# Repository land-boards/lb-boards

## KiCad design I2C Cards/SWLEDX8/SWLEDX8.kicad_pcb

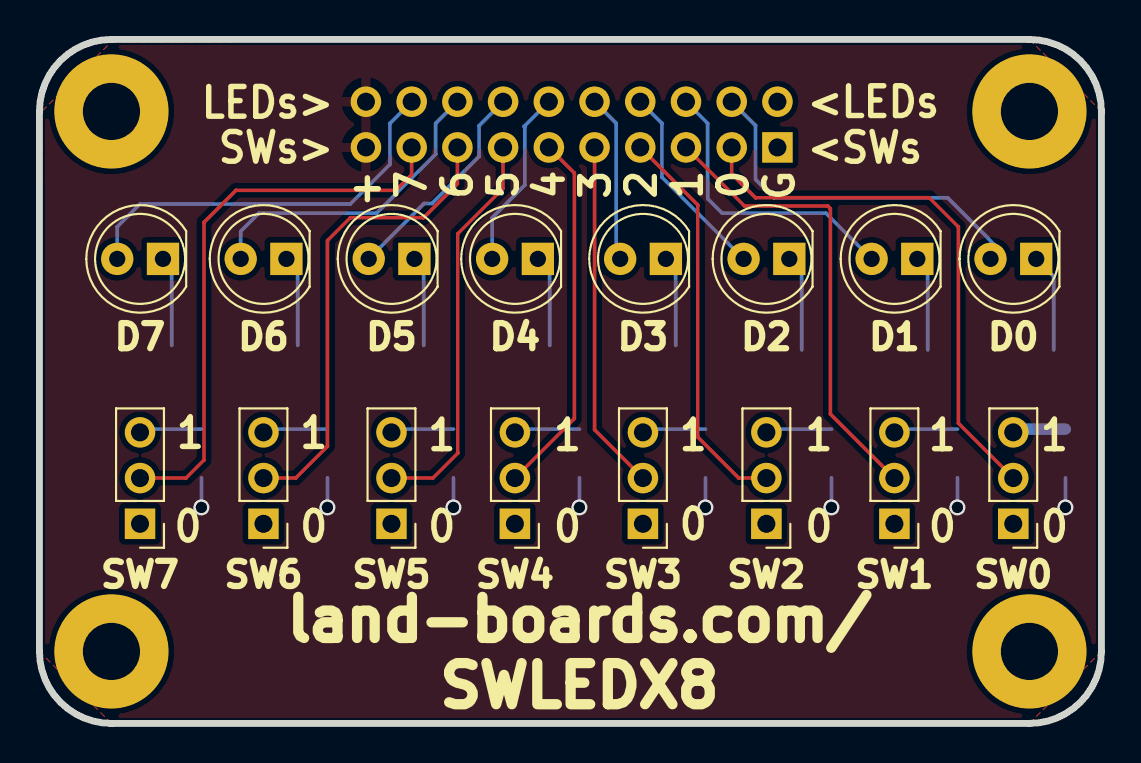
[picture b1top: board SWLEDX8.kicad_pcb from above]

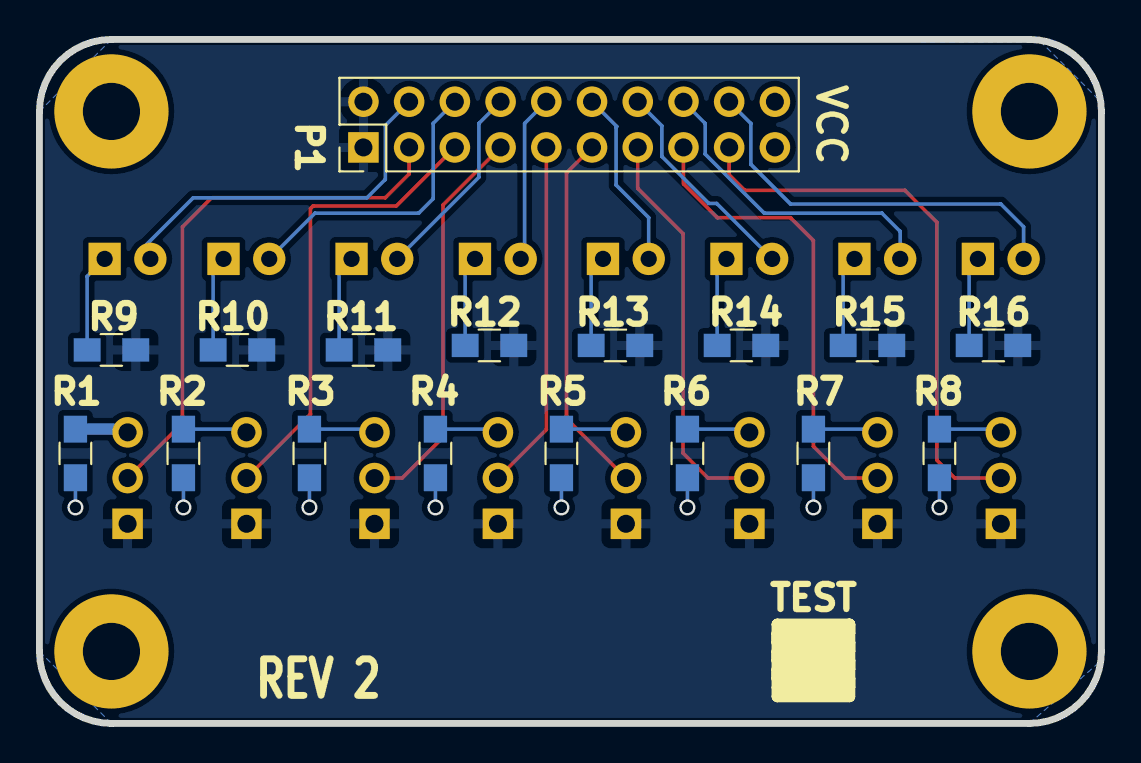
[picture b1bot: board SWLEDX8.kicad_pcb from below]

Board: 2 copper layers, 59.0 x 38.0 mm, 38 parts (17 on the bottom side), 34 nets.

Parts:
D0, D1, D2, D3, D4, D5, D6, D7: LED-fixed; LED_D5.0mm
MTG1, MTG2, MTG3: MTG_HOLE; MTG-4-40
MTG?1: MTG_HOLE; MTG-4-40
P1: CONN_02X10; PinHeader_2x10_P2.54mm_Vertical
R1, R2, R3, R4, R5, R6, R7, R8, R9, R10, R11, R12, R13, R14, R15, R16: R; R_0805_HandSoldering
SW0, SW1, SW2, SW3, SW4, SW5, SW6, SW7: SS12D00; PinHeader_1x03_P2.54mm_Vertical
TEST: COUPON; TEST_BLK-REAR

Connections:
/L0: D0.2 (A), P1.4
/L1: D1.2 (A), P1.6
/L2: D2.2 (A), P1.8
/L3: D3.2 (A), P1.10
/L4: D4.2 (A), P1.12
/L5: D5.2 (A), P1.14
/L6: D6.2 (A), P1.16
/L7: D7.2 (A), P1.18
/S0: P1.3, SW0.2 (B)
/S1: P1.5, SW1.2 (B)
/S2: P1.7, SW2.2 (B)
/S3: P1.9, SW3.2 (B)
/S4: P1.11, SW4.2 (B)
/S5: P1.13, SW5.2 (B)
/S6: P1.15, SW6.2 (B)
/S7: P1.17, SW7.2 (B)
GND: P1.1, P1.2, R9.1, R10.1, R11.1, R12.1, R13.1, R14.1, R15.1, R16.1, SW0.1 (A), SW1.1 (A), SW2.1 (A), SW3.1 (A), SW4.1 (A), SW5.1 (A), SW6.1 (A), SW7.1 (A)
unnamed: D0.1 (K), R9.2
unnamed: D1.1 (K), R10.2
unnamed: D2.1 (K), R11.2
unnamed: D3.1 (K), R12.2
unnamed: D4.1 (K), R13.2
unnamed: D5.1 (K), R14.2
unnamed: D6.1 (K), R15.2
unnamed: D7.1 (K), R16.2
unnamed: R1.1, SW0.3 (C)
unnamed: R2.1, SW1.3 (C)
unnamed: R3.1, SW2.3 (C)
unnamed: R4.1, SW3.3 (C)
unnamed: R5.1, SW4.3 (C)
unnamed: R6.1, SW5.3 (C)
unnamed: R7.1, SW6.3 (C)
unnamed: R8.1, SW7.3 (C)
VCC: P1.19, P1.20, R1.2, R2.2, R3.2, R4.2, R5.2, R6.2, R7.2, R8.2

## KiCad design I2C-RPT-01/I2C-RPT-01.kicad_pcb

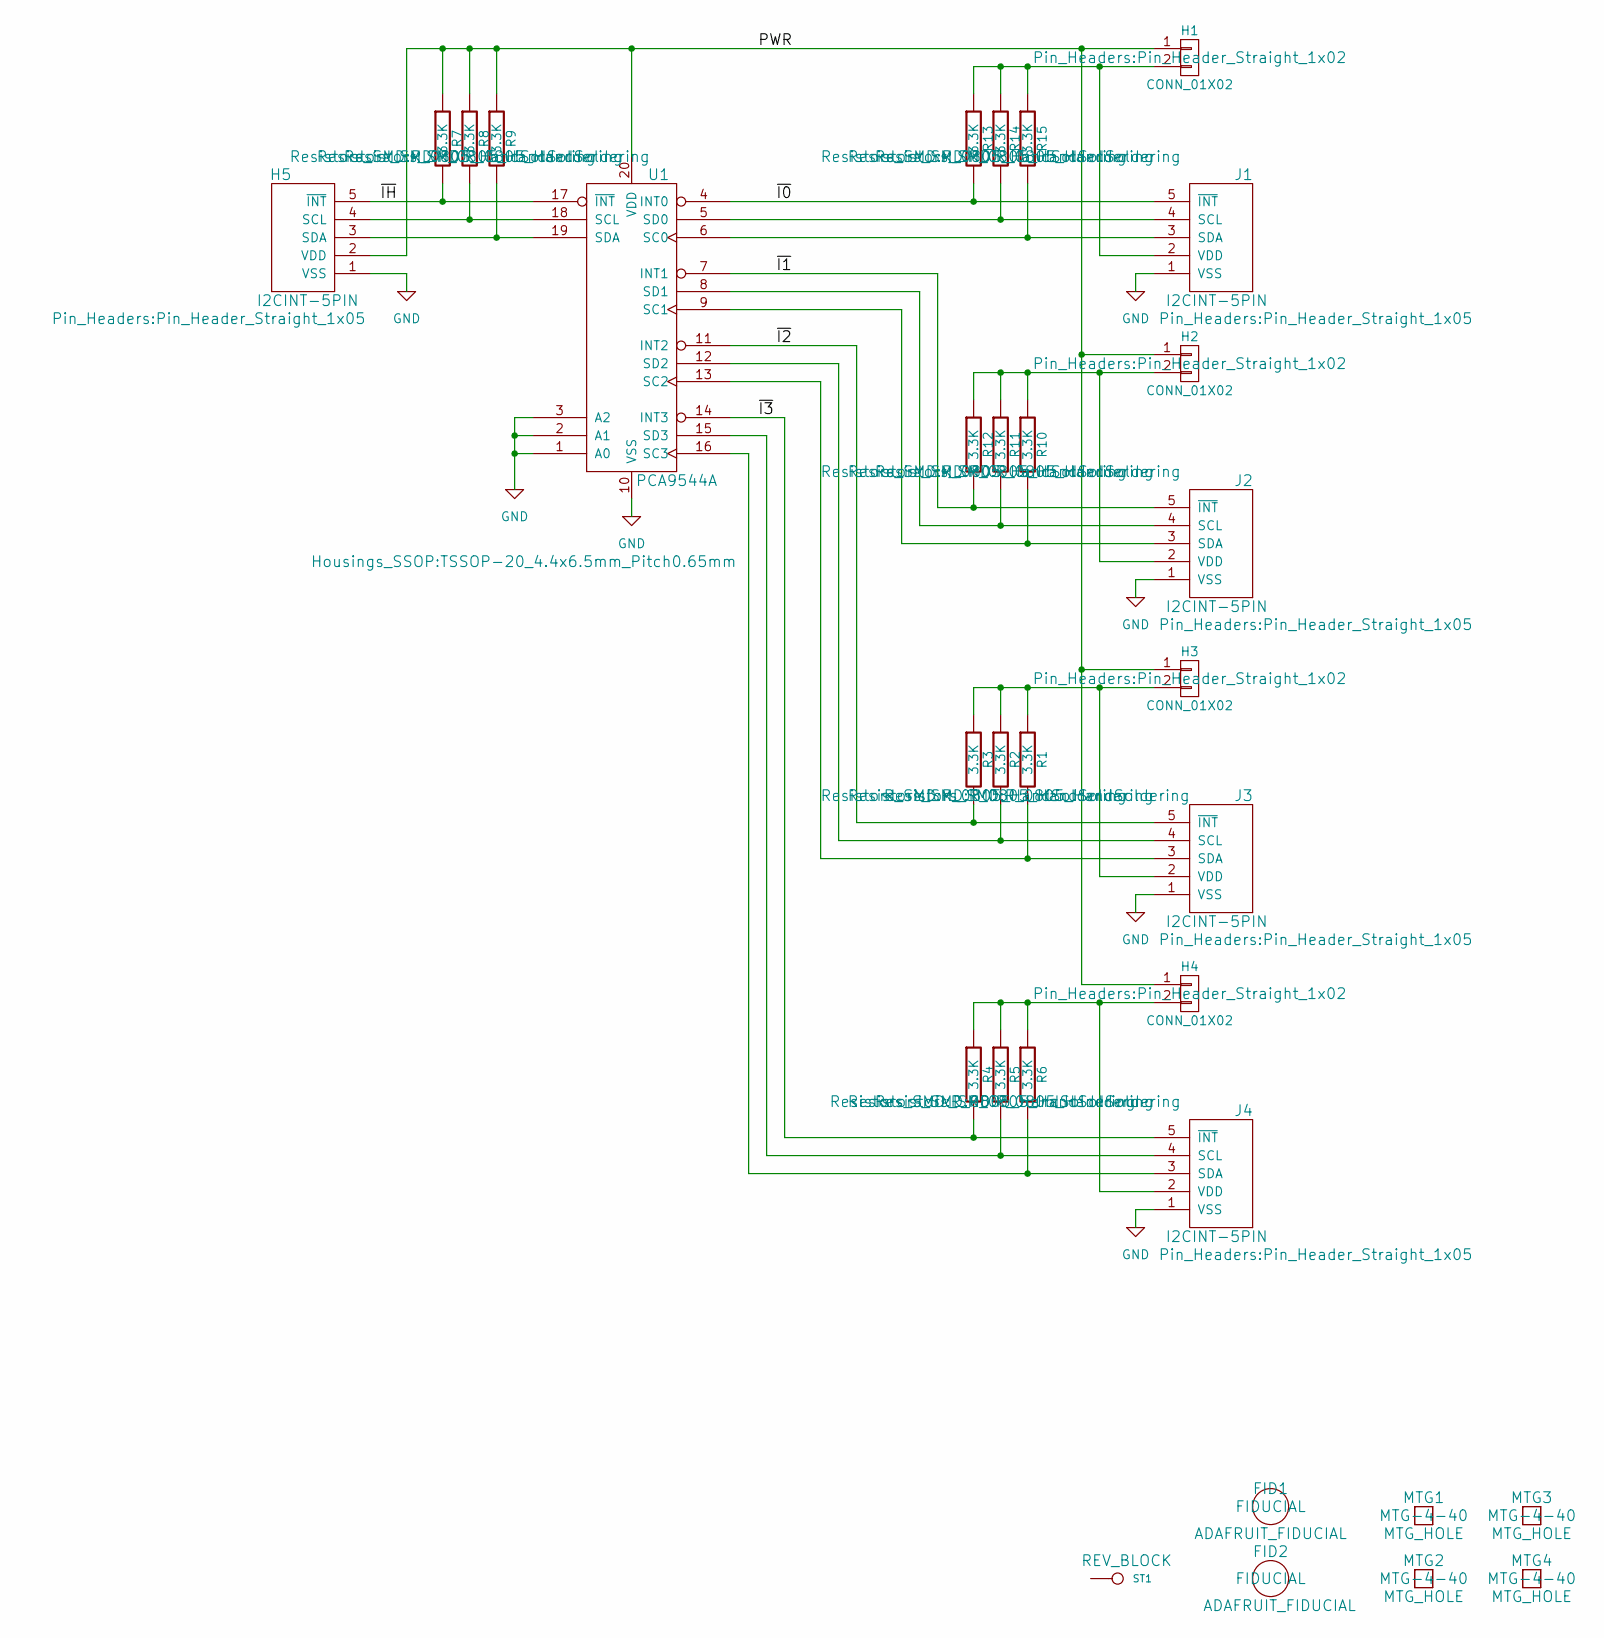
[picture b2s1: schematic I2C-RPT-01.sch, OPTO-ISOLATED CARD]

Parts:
FID1, FID2: ADAFRUIT_FIDUCIAL; FIDUCIAL
H1, H2, H3, H4: CONN_01X02; Pin_Header_Straight_1x02
H5: I2CINT-5PIN; Pin_Header_Straight_1x05
J1, J2, J3, J4: I2CINT-5PIN; Pin_Header_Straight_1x05
MTG1, MTG2, MTG3, MTG4: MTG_HOLE; MTG-4-40
R1, R2, R3, R4, R5, R6, R7, R8, R9, R10, R11, R12, R13, R14, R15: 3.3K; R_0805_HandSoldering
ST1: CONN_1; REV_BLOCK
U1: PCA9544A; TSSOP-20_4.4x6.5mm_Pitch0.65mm

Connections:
/PWR: H1.1, H2.1, H3.1, H4.1, H5.2 (VDD), R7.1, R8.1, R9.1, U1.20 (VDD); also elsewhere on the board
/~I0: J1.5 (~INT), R13.2, U1.4 (INT0)
/~I1: J2.5 (~INT), R12.2, U1.7 (INT1)
/~I2: J3.5 (~INT), R3.2, U1.11 (INT2)
/~I3: J4.5 (~INT), R4.2, U1.14 (INT3)
/~IH: H5.5 (~INT), R7.2, U1.17 (~INT); also elsewhere on the board
GND: H5.1 (VSS), J1.1 (VSS), J2.1 (VSS), J3.1 (VSS), J4.1 (VSS), U1.1 (A0), U1.2 (A1), U1.3 (A2), U1.10 (VSS); also elsewhere on the board
unnamed: H1.2, J1.2 (VDD), R13.1, R14.1, R15.1
unnamed: H2.2, J2.2 (VDD), R10.1, R11.1, R12.1
unnamed: H3.2, J3.2 (VDD), R1.1, R2.1, R3.1
unnamed: H4.2, J4.2 (VDD), R4.1, R5.1, R6.1
unnamed: J1.3 (SDA), R15.2, U1.6 (SC0)
unnamed: J1.4 (SCL), R14.2, U1.5 (SD0)
unnamed: J2.3 (SDA), R10.2, U1.9 (SC1)
unnamed: J2.4 (SCL), R11.2, U1.8 (SD1)
unnamed: J3.3 (SDA), R1.2, U1.13 (SC2)
unnamed: J3.4 (SCL), R2.2, U1.12 (SD2)
unnamed: J4.3 (SDA), R6.2, U1.16 (SC3)
unnamed: J4.4 (SCL), R5.2, U1.15 (SD3)
unnamed 19: H5.3 (SDA), R9.2, U1.19 (SDA); also elsewhere on the board
unnamed 20: H5.4 (SCL), R8.2, U1.18 (SCL); also elsewhere on the board

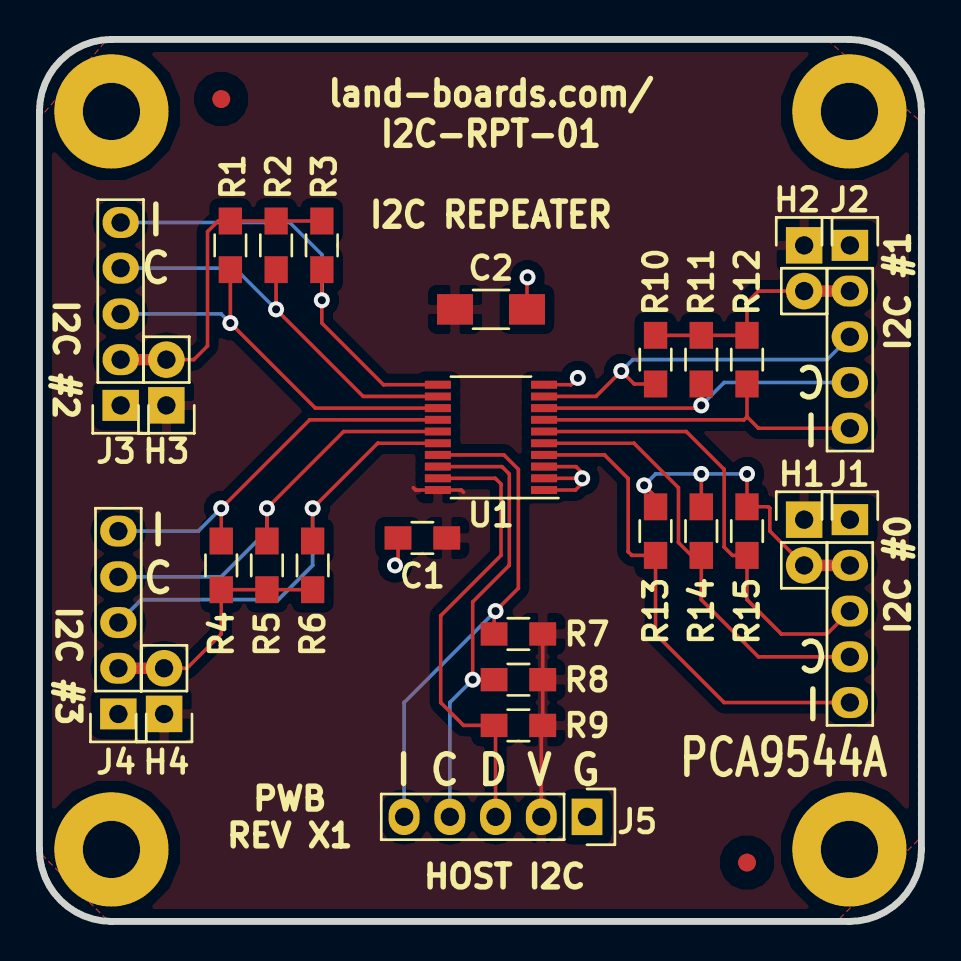
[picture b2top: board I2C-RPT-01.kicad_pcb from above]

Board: 2 copper layers, 49.0 x 49.0 mm, 35 parts (1 on the bottom side), 21 nets.

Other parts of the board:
C1: C; R_0805_HandSoldering
C2: C; R_1206_HandSoldering
J5: I2CINT-5PIN; Pin_Header_Straight_1x05
TESTED: VAL**; TEST_BLK-REAR

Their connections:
/PWR: C1.1, C2.1, J5.2; also elsewhere on the board
/~IH: J5.5; also elsewhere on the board
GND: C1.2, C2.2, J5.1; also elsewhere on the board
unnamed 19: J5.3; also elsewhere on the board
unnamed 20: J5.4; also elsewhere on the board

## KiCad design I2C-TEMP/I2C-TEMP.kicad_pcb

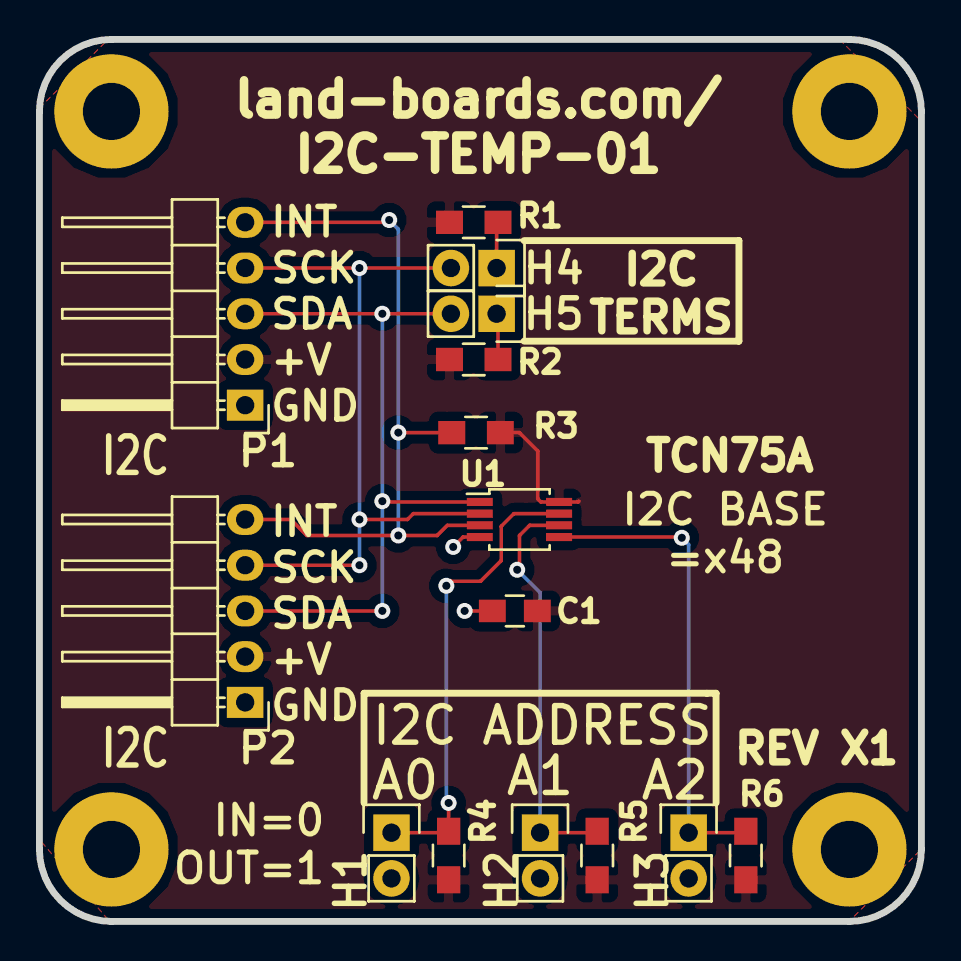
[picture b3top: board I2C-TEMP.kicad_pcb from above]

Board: 2 copper layers, 49.0 x 49.0 mm, 20 parts (0 on the bottom side), 10 nets.

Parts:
C1: 0.1uF; C_0805_HandSoldering
H1, H2, H3, H4, H5: CONN_2; Pin_Header_Straight_1x02
MTG5, MTG6, MTG7: MTG_HOLE; MTG-4-40
MTG?1: MTG_HOLE; MTG-4-40
P1, P2: CONN_01X05; Pin_Header_Angled_1x05
R1, R2, R3, R4, R5, R6: 10K; R_0805_HandSoldering
TEST: TEST; TEST_BLK-REAR
U1: TVN75A; MSOP-8_3x3mm_Pitch0.65mm

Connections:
+5V: C1.1, P1.2, P2.2, R1.1, R2.1, R3.1, R4.1, R5.1, R6.1, U1.8
/A0: H1.1, R4.2, U1.7
/A1: H2.1, R5.2, U1.6
/A2: H3.1, R6.2, U1.5
/INT: P1.5, P2.5, R3.2, U1.3
/SCK: H4.2, P1.4, P2.4, U1.2
/SDA: H5.2, P1.3, P2.3, U1.1
GND: C1.2, H1.2, H2.2, H3.2, P1.1, P2.1, U1.4
unnamed: H4.1, R1.2
unnamed: H5.1, R2.2

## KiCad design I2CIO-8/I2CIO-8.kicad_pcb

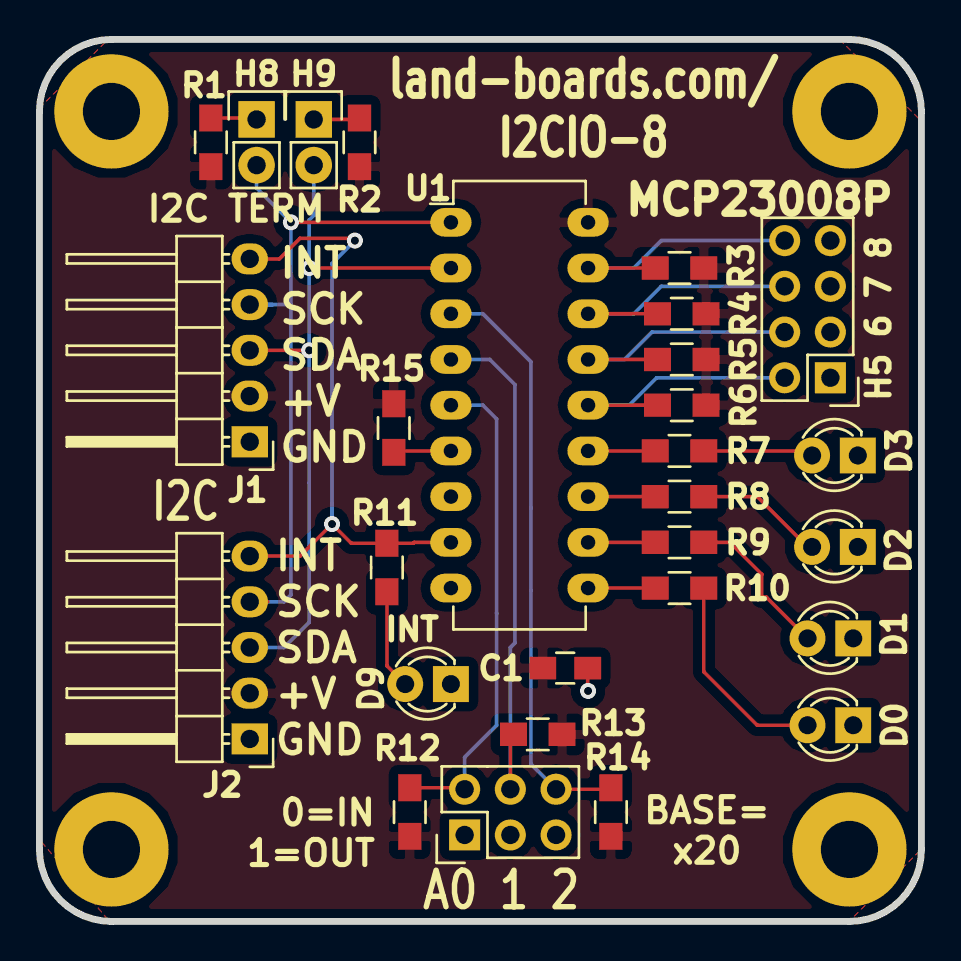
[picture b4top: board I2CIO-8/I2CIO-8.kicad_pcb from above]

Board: 2 copper layers, 49.0 x 49.0 mm, 33 parts (0 on the bottom side), 24 nets.

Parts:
C1: 0.1uF; C_0805_HandSoldering
D0, D1, D2, D3, D9: LED-fixed; LED-3MM
H4: CONN_02X04; Pin_Header_Straight_2x04
H5: CONN_02X03; Pin_Header_Straight_2x03
H8, H9: CONN_2; Pin_Header_Straight_1x02
J1, J2: CONN_01X05; Pin_Header_Angled_1x05
MTG5, MTG6, MTG7: MTG_HOLE; MTG-4-40
MTG?1: MTG_HOLE; MTG-4-40
R1, R2, R12, R13, R14, R15: 10K; R_0805_HandSoldering
R3, R4, R5, R6, R7, R8, R9, R10, R11: 330; R_0805_HandSoldering
TEST: TEST; TEST_BLK-REAR
U1: MCP23008P; DIP-18_W7.62mm_LongPads

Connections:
+5V: C1.1, J1.2, J2.2, R1.1, R2.1, R3.2, R4.2, R5.2, R6.2, R12.1, R13.1, R14.1, R15.1, U1.18
/A0: H5.2, R12.2, U1.5
/A1: H5.4, R13.2, U1.4
/A2: H5.6, R14.2, U1.3
/RST: R15.2, U1.6
/SCK: H8.2, J1.4, J2.4, U1.1
/SDA: H9.2, J1.3, J2.3, U1.2
GND: C1.2, D0.1, D1.1, D2.1, D3.1, D9.1, H4.1, H4.3, H4.5, H4.7, H5.1, H5.3, H5.5, J1.1, J2.1, U1.9
unnamed: D0.2, R10.1
unnamed: D1.2, R9.1
unnamed: D2.2, R8.1
unnamed: D3.2, R7.1
unnamed: D9.2, R11.1
unnamed: H4.2, R6.1, U1.14
unnamed: H4.4, R5.1, U1.15
unnamed: H4.6, R4.1, U1.16
unnamed: H4.8, R3.1, U1.17
unnamed: H8.1, R1.2
unnamed: H9.1, R2.2
unnamed: J1.5, J2.5, R11.2, U1.8
unnamed: R7.2, U1.13
unnamed: R8.2, U1.12
unnamed: R9.2, U1.11
unnamed: R10.2, U1.10

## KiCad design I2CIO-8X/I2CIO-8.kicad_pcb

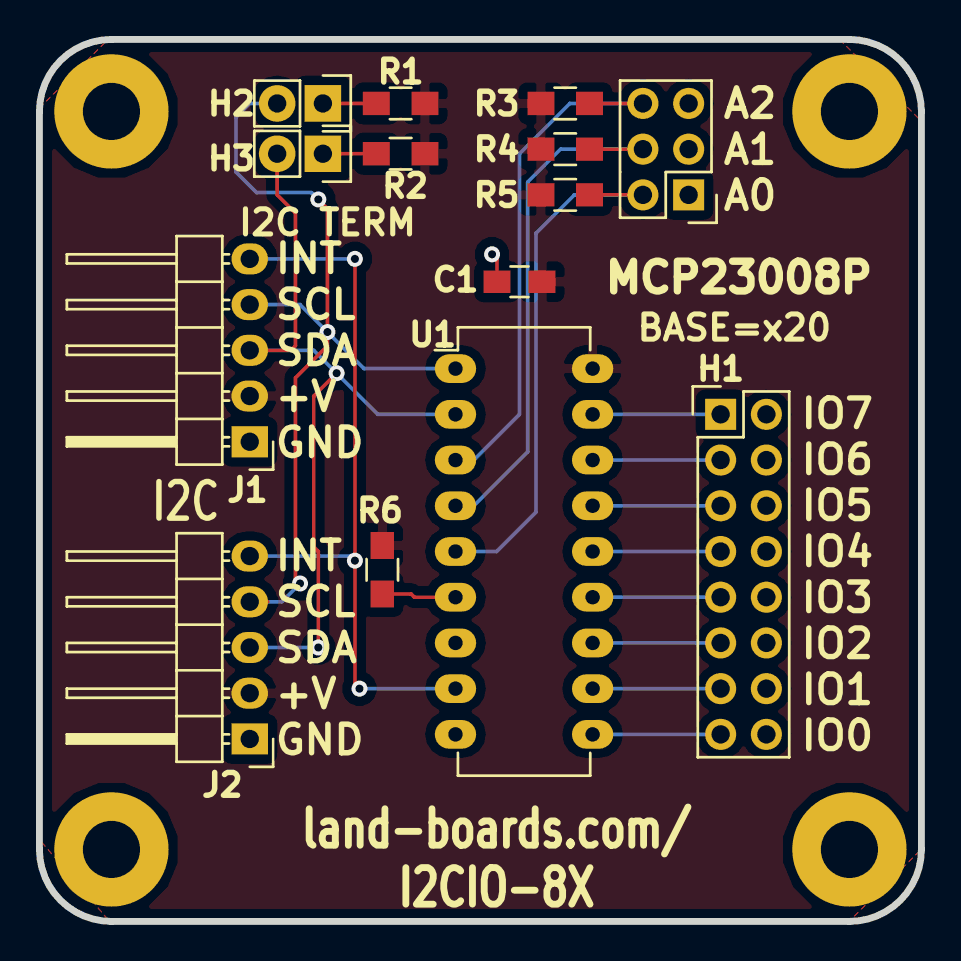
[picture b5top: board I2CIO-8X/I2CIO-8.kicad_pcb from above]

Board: 2 copper layers, 49.0 x 49.0 mm, 19 parts (0 on the bottom side), 19 nets.

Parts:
C1: 0.1uF; C_0805_HandSoldering
H1: CONN_02X08; Pin_Header_Straight_2x08
H2, H3: CONN_2; Pin_Header_Straight_1x02
H4: CONN_02X03; Pin_Header_Straight_2x03
J1, J2: CONN_01X05; Pin_Header_Angled_1x05
MTG5, MTG6, MTG7: MTG_HOLE; MTG-4-40
MTG?1: MTG_HOLE; MTG-4-40
R1, R2, R3, R4, R5, R6: 10K; R_0805_HandSoldering
TEST1: TEST; TEST_BLK-REAR
U1: MCP23008P; DIP-18_W7.62mm_LongPads

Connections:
+5V: C1.1, J1.2, J2.2, R1.1, R2.1, R3.1, R4.1, R5.1, R6.1, U1.18
/A0: H4.2, R5.2, U1.5
/A1: H4.4, R4.2, U1.4
/A2: H4.6, R3.2, U1.3
/INT: J1.5, J2.5, U1.8
/IO0: H1.15, U1.10
/IO1: H1.13, U1.11
/IO2: H1.11, U1.12
/IO3: H1.9, U1.13
/IO4: H1.7, U1.14
/IO5: H1.5, U1.15
/IO6: H1.3, U1.16
/IO7: H1.1, U1.17
/RST: R6.2, U1.6
/SCK: H2.2, J1.4, J2.4, U1.1
/SDA: H3.2, J1.3, J2.3, U1.2
GND: C1.2, H1.2, H1.4, H1.6, H1.8, H1.10, H1.12, H1.14, H1.16, H4.1, H4.3, H4.5, J1.1, J2.1, U1.9
unnamed: H2.1, R1.2
unnamed: H3.1, R2.2
